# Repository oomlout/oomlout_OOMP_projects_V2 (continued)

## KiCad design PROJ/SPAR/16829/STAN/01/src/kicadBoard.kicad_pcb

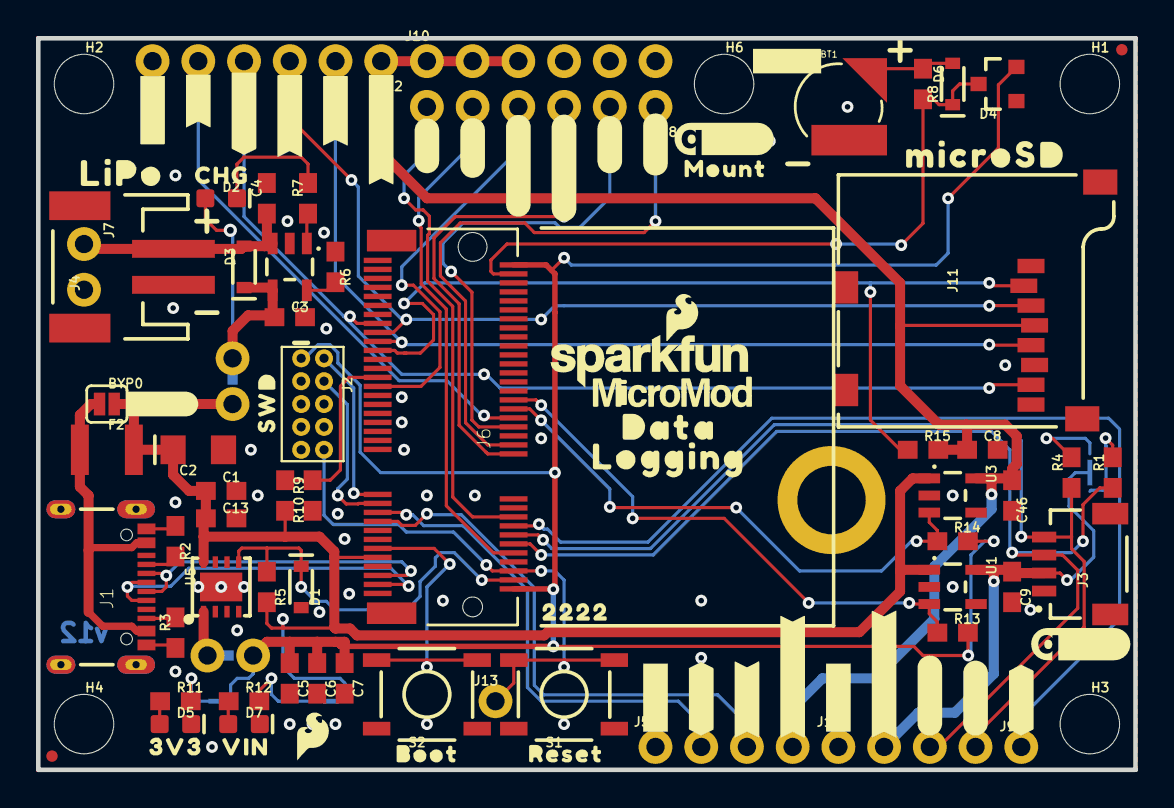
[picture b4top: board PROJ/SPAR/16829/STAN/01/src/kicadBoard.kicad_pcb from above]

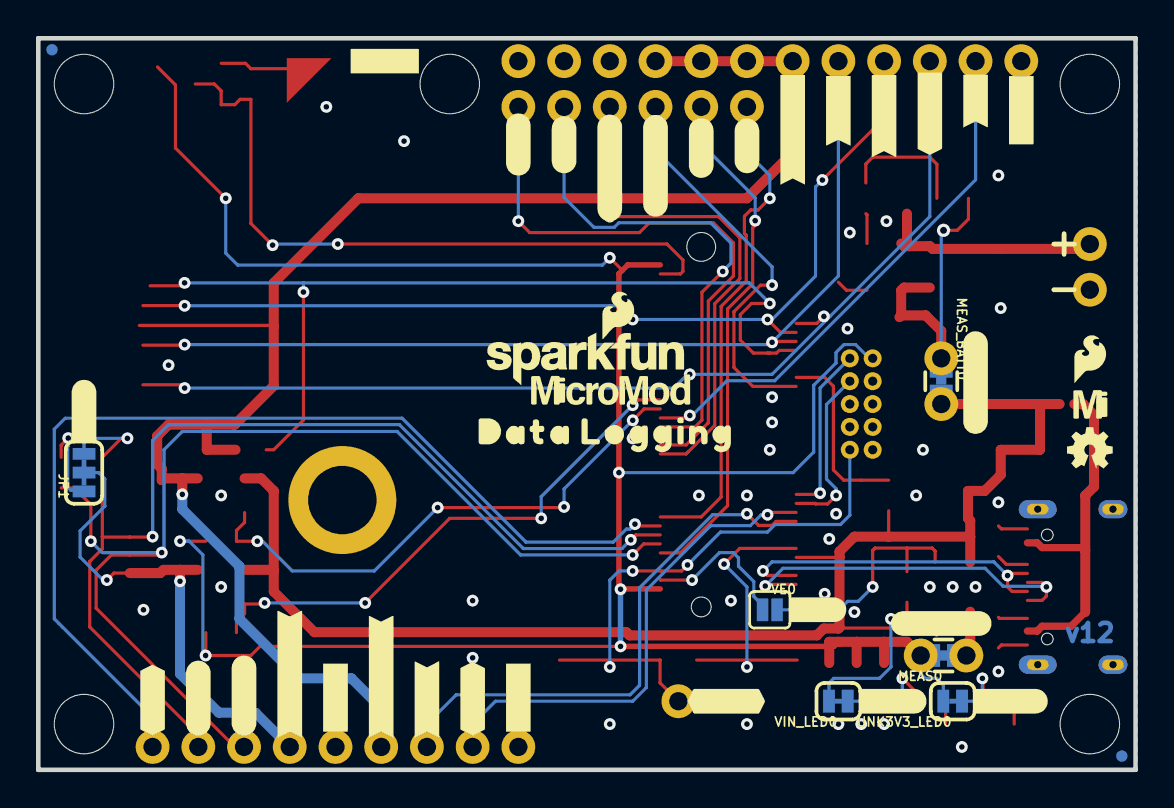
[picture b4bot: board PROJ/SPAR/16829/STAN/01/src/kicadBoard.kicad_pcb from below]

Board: 2 copper layers, 61.0 x 40.6 mm, 149 parts (44 on the bottom side), 49 nets.

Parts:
BT1: ML414H; ML414H_IV01E
BYP0: JUMPER-SMT_2_NO_SILK; SMT-JUMPER_2_NO_SILK
C1, C6, C46: 0.1uF; 0603
C2: 10uF; EIA3216
C3, C4: 4.7uF; 0603
C5, C8, C9: 1.0uF; 0603
C7, C13: 0.22uF; 0603
D1: 3.3V; SOD-323
D2, D7: Yellow; LED-0603
D3, D6: 3A/10V/280mV; SOD-323
D4: BAS70-05; SOT23-3
D5: RED; LED-0603
F2: 6V/2A; 1210
FD1, FD2, FD3, FD4: FIDUCIALUFIDUCIAL; FIDUCIAL-MICRO
FRAME1: FRAME-LEDGER; CREATIVE_COMMONS
H1, H2, H3, H4, H6: STAND-OFF
H5: STAND-OFF-REFLOW2.5MM_TALL; STAND-OFF-REFLOW-M2.5
J1: USB-C-16P-2LAYER-PADS
J2: JTAG; 2X5-PTH-1.27MM
J3: QWIIC_RIGHT_ANGLE; JST04_1MM_RA
J4: JST-2-SMD
J5: UART; 1X04_NO_SILK
J6: MICROMOD-2222-C; M.2-CONNECTOR-E
J7: 1X02_NO_SILK
J8: Dedicated; 1X06_NO_SILK
J9, J13: 1X01_NO_SILK
J10: 1X06_NO_SILK
J11: microSD; MICRO-SD-SOCKET
J12: SPI; 1X06_NO_SILK
J14: I2C; 1X04_NO_SILK
JP1: SMT-JUMPER_3_2-NC_TRACE_SILK
LOGO1, LOGO4: SFE_LOGO_NAME_FLAME.1_INCH; SFE_LOGO_NAME_FLAME_.1
LOGO2, LOGO5: QWIIC_LOGO_CONNECTOR; QWIIC_5.5MM
LOGO3: OSHW-LOGOMINI; OSHW-LOGO-MINI
MEAS0: COMBO-JUMPER_2_NC_TRACE
MEAS_BATT0: COMBO-JUMPER_2_NC_TRACE
R1, R4, R6: 2.2k; 0603
R2, R3: 5.1k; 0603
R5, R13, R14, R15: 100k; 0603
R7, R11: 1k; 0603
R8: 3.3k; 0603
R9: 10k; 0603
R10: 20k; 0603
R12: 4.7k; 0603
S1: Reset; TACTILE_SWITCH_SMD_5.2MM
S2: BOOT; TACTILE_SWITCH_SMD_5.2MM
U1, U3: 3.3V; SOT23-5
U2: MCP73831; SOT23-5
U5: AP7361C-33; UDFN-8
U$1, U$66: SFE_LOGO_FLAME_.1
U$2, U$76: #D1#0
U$3, U$77: #D0#0
U$4: #3V3#2
U$5: #BATT#0
U$6, U$18, U$24, U$27, U$32, U$34, U$36, U$42: #GND#0
U$7, U$8: #SCK#0
U$9, U$81: #PWM1#1
U$10, U$80: #PWM0#0
U$11: MICROSD0
U$12, U$79: #A1#2
U$13, U$78: #A0#3
U$14: MOUNT0
U$15: LIPO0
U$16, U$23: DATA0
U$17, U$86: #RX1#1
U$19, U$26: LOGGING1
U$20: 22220
U$21, U$89: #TX1#2
U$22: #I2C#0
U$25, U$90: #G1#3V3#0
U$28: #MEAS#3
U$29, U$83: #G2#3V3#3
U$30: #RST#0
U$31, U$88: #SDA#4
U$33: #VIN#1
U$35, U$87: #SCL#5
U$37, U$63: MICROMOD_LOGO_.35
U$38, U$82: ##INT##6
U$39, U$40: #CIPO#0
U$41: #VE#0
U$50, U$51: ##CS##0
U$62: MICROMOD_MI_LOGO_.35
U$64, U$65: #G1_3V3#0
U$72, U$73: #COPI#0
U$91: BOOT0
U$92: RESET1
U$93: 3V30
U$94: VIN1
U$95: #BYP#3
U$96: CHG1
U$97: SWD0
UNK3V3_LED0: SMT-JUMPER_2_NC_TRACE_SILK
VE0: SMT-JUMPER_2_NO_SILK
VIN_LED0: SMT-JUMPER_2_NC_TRACE_SILK

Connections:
3.3V: C5.1, C6.1, C7.1, D4.2, J2.1, J6.2, J6.74, MEAS0.2, MEAS0.4, R13.2, R14.2, UNK3V3_LED0.2
3.3V_EN: J6.4, VE0.1
3.3V_EN_VE: D1.C, R5.1, U5.5, VE0.2
3.3V_LP: C8.1, C46.1, J5.4, J10.1, J10.2, J10.3, J11.VCC, J12.1, R15.2, U3.5
5V: C3.1, D2.A, D3.C, MEAS_BATT0.1, MEAS_BATT0.3, U2.4
A0: J6.34, J8.1
A1: J6.38, J8.2
CHG_LED: R7.1, U2.1
D0: J6.10, J8.5
D1: J6.18, J8.6
GND: BT1.-, C1.2, C2.-, C3.2, C4.2, C5.2, C6.2, C7.2, C8.2, C9.2, C13.2, C46.2, D1.A, D5.C, D7.C, H5.1, J1.GND, J1.GND2, J2.3, J2.5, J2.9, J3.1, J4.1, J5.1, J6.1, J6.7, J6.33, J6.36, J6.39, J6.45, J6.75, J7.2, J10.4, J10.5, J10.6, J11.CD1, J11.GND, J11.GND1, J11.GND3, J12.6, J14.1, R2.1, R3.1, R6.1, R9.1, S1.1, S1.2, S2.1, S2.2, U1.2, U2.2, U3.2, U5.4, U5.EP
HEADER_~CS: J6.40, J12.5
I2C_SCL: J3.4, J6.14, J14.4, R4.1
I2C_SDA: J3.3, J6.12, J14.3, R1.1
I2C_~INT: J6.16, J9.1
unnamed: MEAS0.1, MEAS0.3, U5.1
unnamed: JP1.3, R4.2
unnamed: JP1.1, R1.2
unnamed: D2.C, R7.2
unnamed: D5.A, R11.1
unnamed: R11.2, UNK3V3_LED0.1
unnamed: R6.2, U2.5
unnamed: R12.2, VIN_LED0.1
unnamed: D7.A, R12.1
unnamed: J1.A5, R2.2
unnamed: J1.B5, R3.2
unnamed: BT1.+, D6.A, R8.1
PERIPHERAL_PWR_CTRL: J6.42, R14.1, U3.3
PWM0: J6.32, J8.3
PWM1: J6.47, J8.4
QWIIC_PWR: C9.1, J3.2, J14.2, JP1.2, U1.5
QWIIC_PWR_CTRL: J6.44, R13.1, U1.3
RTC_3V: D4.3, D6.C, J6.72, R8.2
RX1: J5.2, J6.19
SD_~CS: J6.55, J11.CS/DAT3, R15.1
SPI_CIPO: J6.61, J11.DO/DAT0, J12.4
SPI_COPI: J6.59, J11.DI/CMD, J12.3
SPI_SCK: J6.57, J11.SCLK, J12.2
SWDCK: J2.4, J6.21
SWDIO: J2.2, J6.23
TX1: J5.3, J6.17
USB_D+: J1.A6, J1.B6, J6.3
USB_D-: J1.A7, J1.B7, J6.5
VIN: BYP0.2, C1.1, C2.+, C13.1, F2.2, J6.9, MEAS_BATT0.2, MEAS_BATT0.4, R5.2, R10.2, U1.1, U3.1, U5.8, VIN_LED0.2
VIN/3: J6.49, R9.2, R10.1
V_BATT: C4.1, D3.A, J4.2, J7.1, U2.3
V_USB: BYP0.1, F2.1, J1.VBUS1, J1.VBUS2
~BOOT: J6.11, S2.3, S2.4
~RESET: J2.10, J6.6, J13.1, S1.3, S1.4

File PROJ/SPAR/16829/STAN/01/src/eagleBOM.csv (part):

"Part";"Value";"Device";"Package";"Description";"DESIGNER";"PROD_ID";"REV";"SF_ID";"VALUE";
"3V3_LED";"";"JUMPER-SMT_2_NC_TRACE_SILK";"SMT-JUMPER_2_NC_TRACE_SILK";"Normally closed trace jumper";"";"";"";"";"";
"BT1";"ML414H";"ML414H_IV01E_BATTERY";"ML414H_IV01E";"SEIKO ML414H-IV01E Reflowable Lithium Battery";"";"BATT-14267";"";"";"";
"BYP";"JUMPER-SMT_2_NO_SILK";"JUMPER-SMT_2_NO_SILK";"SMT-JUMPER_2_NO_SILK";"Normally open jumper";"";"";"";"";"";
"C1";"0.1uF";"0.1UF-0603-25V-(+80/-20%)";"0603";"0.1µF ceramic capacitors";"";"CAP-00810";"";"";"0.1uF";
"C2";"10uF";"10UF-POLAR-EIA3216-16V-10%(TANT)";"EIA3216";"10.0µF polarized capacitors";"";"CAP-00811";"";"";"10uF";
"C3";"4.7uF";"4.7UF-0603-35V-(20%)";"0603";"4.7µF ceramic capacitors";"";"CAP-14106";"";"";"4.7uF";
"C4";"4.7uF";"4.7UF-0603-6.3V-(10%)";"0603";"4.7µF ceramic capacitors";"";"CAP-08280";"";"";"4.7uF";
"C5";"1.0uF";"1.0UF-0603-16V-10%";"0603";"1µF ceramic capacitors";"";"CAP-00868";"";"";"1.0uF";
"C6";"0.1uF";"0.1UF-0603-25V-(+80/-20%)";"0603";"0.1µF ceramic capacitors";"";"CAP-00810";"";"";"0.1uF";
"C7";"0.22uF";"0.22UF-0603-25V-10%";"0603";"0.22µF ceramic capacitors";"";"CAP-07822";"";"";"0.22uF";
"C8";"1.0uF";"1.0UF-0603-16V-10%";"0603";"1µF ceramic capacitors";"";"CAP-00868";"";"";"1.0uF";
"C9";"1.0uF";"1.0UF-0603-16V-10%";"0603";"1µF ceramic capacitors";"";"CAP-00868";"";"";"1.0uF";
"C13";"0.22uF";"0.22UF-0603-25V-10%";"0603";"0.22µF ceramic capacitors";"";"CAP-07822";"";"";"0.22uF";
"C46";"0.1uF";"0.1UF-0603-25V-(+80/-20%)";"0603";"0.1µF ceramic capacitors";"";"CAP-00810";"";"";"0.1uF";
"D1";"3.3V";"DIODE-ZENER-MM3Z3V3T1G";"SOD-323";"Zener Diode";"";"DIO-11284";"";"";"3.3V";
"D2";"Yellow";"LED-YELLOW0603";"LED-0603";"Yellow SMD LED";"";"DIO-09003";"";"";"Yellow";
"D3";"3A/10V/280mV";"DIODE-SCHOTTKY-BAT60A";"SOD-323";"Schottky diode";"";"DIO-14072";"";"";"3A/10V/280mV";
"D4";"BAS70-05";"DIODE-SCHOTTKY-DUAL";"SOT23-3";"Diodes Incorporated - BAS70-05 Dual Schottky Diode";"";"DIO-14829";"";"";"BAS70-05";
"D5";"RED";"LED-RED0603";"LED-0603";"Red SMD LED";"";"DIO-00819";"";"";"RED";
"D6";"3A/10V/280mV";"DIODE-SCHOTTKY-BAT60A";"SOD-323";"Schottky diode";"";"DIO-14072";"";"";"3A/10V/280mV";
"D7";"Yellow";"LED-YELLOW0603";"LED-0603";"Yellow SMD LED";"";"DIO-09003";"";"";"Yellow";
"F2";"6V/2A";"PPTC_6V2A";"1210";"Resettable Fuse PPTC";"";"RES-14313";"";"";"6V/2A";
"FD1";"FIDUCIALUFIDUCIAL";"FIDUCIALUFIDUCIAL";"FIDUCIAL-MICRO";"Fiducial Alignment Points";"";"";"";"";"";
"FD2";"FIDUCIALUFIDUCIAL";"FIDUCIALUFIDUCIAL";"FIDUCIAL-MICRO";"Fiducial Alignment Points";"";"";"";"";"";
"FD3";"FIDUCIALUFIDUCIAL";"FIDUCIALUFIDUCIAL";"FIDUCIAL-MICRO";"Fiducial Alignment Points";"";"";"";"";"";
"FD4";"FIDUCIALUFIDUCIAL";"FIDUCIALUFIDUCIAL";"FIDUCIAL-MICRO";"Fiducial Alignment Points";"";"";"";"";"";
"FRAME1";"FRAME-LEDGER";"FRAME-LEDGER";"CREATIVE_COMMONS";"Schematic Frame - Ledger";"";"";"";"";"";
"H1";"STAND-OFF";"STAND-OFF";"STAND-OFF";"Stand Off";"";"";"";"";"";
"H2";"STAND-OFF";"STAND-OFF";"STAND-OFF";"Stand Off";"";"";"";"";"";
"H3";"STAND-OFF";"STAND-OFF";"STAND-OFF";"Stand Off";"";"";"";"";"";
"H4";"STAND-OFF";"STAND-OFF";"STAND-OFF";"Stand Off";"";"";"";"";"";
"H5";"STAND-OFF-REFLOW2.5MM_TALL";"STAND-OFF-REFLOW2.5MM_TALL";"STAND-OFF-REFLOW-M2.5";"Stand Off Reflow Compatible";"";"HW-14899";"";"";"";
"J1";"";"USB_C_2-LAYER_PADS";"USB-C-16P-2LAYER-PADS";"USB Type C 16Pin Connector";"";"CONN-14122";"";"";"";
"J2";"JTAG";"CORTEX_JTAG_DEBUG_MINIMUM_PTH";"2X5-PTH-1.27MM";"Cortex Debug Connector - 10 pin";"";"";"";"";"";
"J3";"QWIIC_RIGHT_ANGLE";"QWIIC_CONNECTORJS-1MM";"JST04_1MM_RA";"SparkFun I2C Standard Qwiic Connector";"";"CONN-13694";"";"";"QWIIC_RIGHT_ANGLE";
"J4";"";"JST_2MM_MALE";"JST-2-SMD";"JST 2MM MALE RA CONNECTOR";"";"CONN-11443";"";"PRT-08612";"";
"J5";"UART";"CONN_041X04_NO_SILK";"1X04_NO_SILK";"Multi connection point. Often used as Generic Header-pin footprint for 0.1 inch spaced/style header connections";"";"CONN-09696";"";"";"";
"J6";"MICROMOD-2222-C";"MICROMOD-2222-C";"M.2-CONNECTOR-E";"MicroMod Connector";"";"CONN-14877";"";"";"";
"J7";"";"CONN_021X02_NO_SILK";"1X02_NO_SILK";"Multi connection point. Often used as Generic Header-pin footprint for 0.1 inch spaced/style header connections";"";"";"";"";"";
"J8";"Dedicated";"CONN_06NO_SILK_NO_POP";"1X06_NO_SILK";"Multi connection point. Often used as Generic Header-pin footprint for 0.1 inch spaced/style header connections";"";"";"";"";"";
"J9";"";"CONN_01PTH_NO_SILK_YES_STOP";"1X01_NO_SILK";"Single connection point. Often used as Generic Header-pin footprint for 0.1 inch spaced/style header connections";"";"";"";"";"";
"J10";"";"CONN_06NO_SILK_NO_POP";"1X06_NO_SILK";"Multi connection point. Often used as Generic Header-pin footprint for 0.1 inch spaced/style header connections";"";"";"";"";"";
"J11";"microSD";"MICRO-SD-SDIOPUSH-PUSH";"MICRO-SD-SOCKET";"microSD Socket for Transflash";"";"CONN-07820";"";"";"";
"J12";"SPI";"CONN_06NO_SILK_NO_POP";"1X06_NO_SILK";"Multi connection point. Often used as Generic Header-pin footprint for 0.1 inch spaced/style header connections";"";"";"";"";"";
"J13";"";"CONN_01PTH_NO_SILK_YES_STOP";"1X01_NO_SILK";"Single connection point. Often used as Generic Header-pin footprint for 0.1 inch spaced/style header connections";"";"";"";"";"";
"J14";"I2C";"I2C_STANDARD_NO_SILK";"1X04_NO_SILK";"SparkFun I2C Standard Pinout Header";"";"";"";"";"";
"JP1";"";"JUMPER-SMT_3_2-NC_TRACE_SILK";"SMT-JUMPER_3_2-NC_TRACE_SILK";"Normally closed trace jumper (2 of 2 connections)";"";"";"";"";"";
"LOGO1";"SFE_LOGO_NAME_FLAME.1_INCH";"SFE_LOGO_NAME_FLAME.1_INCH";"SFE_LOGO_NAME_FLAME_.1";"SparkFun Font Logo w/ Flame";"";"";"";"";"";
"LOGO2";"QWIIC_LOGO_CONNECTOR";"QWIIC_LOGO_CONNECTOR";"QWIIC_5.5MM";"Qwiic Logos for placement on schematic and PCB. The 5.5mm silk logo is best for placing next to Qwiic connector.";"";"";"";"";"";
"LOGO3";"OSHW-LOGOMINI";"OSHW-LOGOMINI";"OSHW-LOGO-MINI";"Open-Source Hardware (OSHW) Logo";"";"";"";"";"";
"MEAS";"";"JUMPER-COMBO_2_NC_TRACE";"COMBO-JUMPER_2_NC_TRACE";"";"";"";"";"";"";
"MEAS_BATT";"";"JUMPER-COMBO_2_NC_TRACE";"COMBO-JUMPER_2_NC_TRACE";"";"";"";"";"";"";
"R1";"2.2k";"2.2KOHM-0603-1/10W-1%";"0603";"2.2kΩ resistor";"";"RES-08272";"";"";"2.2k";
"R2";"5.1k";"5.1KOHM5.1KOHM-0603-1/10W-1%";"0603";"";"";"RES-12083";"";"";"5.1k";
"R3";"5.1k";"5.1KOHM5.1KOHM-0603-1/10W-1%";"0603";"";"";"RES-12083";"";"";"5.1k";
"R4";"2.2k";"2.2KOHM-0603-1/10W-1%";"0603";"2.2kΩ resistor";"";"RES-08272";"";"";"2.2k";
"R5";"100k";"100KOHM-0603-1/10W-1%";"0603";"100kΩ resistor";"";"RES-07828";"";"";"100k";
"R6";"2.2k";"2.2KOHM-0603-1/10W-1%";"0603";"2.2kΩ resistor";"";"RES-08272";"";"";"2.2k";
"R7";"1k";"1KOHM-0603-1/10W-1%";"0603";"1kΩ resistor";"";"RES-07856";"";"";"1k";
"R8";"3.3k";"3.3KOHM-0603-1/10W-1%";"0603";"3.3kΩ resistor";"";"RES-07851";"";"";"3.3k";
"R9";"10k";"10KOHM-0603-1/10W-1%";"0603";"10kΩ resistor";"";"RES-00824";"";"";"10k";
"R10";"20k";"20KOHM-0603-1/10W-1%";"0603";"20kΩ resistor";"";"RES-09383";"";"";"20k";
"R11";"1k";"1KOHM-0603-1/10W-1%";"0603";"1kΩ resistor";"";"RES-07856";"";"";"1k";
"R12";"4.7k";"4.7KOHM-0603-1/10W-1%";"0603";"4.7kΩ resistor";"";"RES-07857";"";"";"4.7k";
"R13";"100k";"100KOHM-0603-1/10W-1%";"0603";"100kΩ resistor";"";"RES-07828";"";"";"100k";
"R14";"100k";"100KOHM-0603-1/10W-1%";"0603";"100kΩ resistor";"";"RES-07828";"";"";"100k";
"R15";"100k";"100KOHM-0603-1/10W-1%";"0603";"100kΩ resistor";"";"RES-07828";"";"";"100k";
"S1";"Reset";"MOMENTARY-SWITCH-SPST-SMD-5.2-TALL-REDUNDANT";"TACTILE_SWITCH_SMD_5.2MM";"Momentary Switch (Pushbutton) - SPST";"";"SWCH-14139";"";"";"";
"S2";"BOOT";"MOMENTARY-SWITCH-SPST-SMD-5.2-TALL-REDUNDANT";"TACTILE_SWITCH_SMD_5.2MM";"Momentary Switch (Pushbutton) - SPST";"";"SWCH-14139";"";"";"";
"U1";"3.3V";"V_REG_AP2112K-3.3V";"SOT23-5";"AP2112 - 600mA CMOS LDO Regulator w/ Enable";"";"VREG-12457";"";"";"3.3V";
"U2";"MCP73831";"MCP73831";"SOT23-5";"MCP73831T Li-Ion, Li-Pol Controller";"";"IC-09995";"";"";"";
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
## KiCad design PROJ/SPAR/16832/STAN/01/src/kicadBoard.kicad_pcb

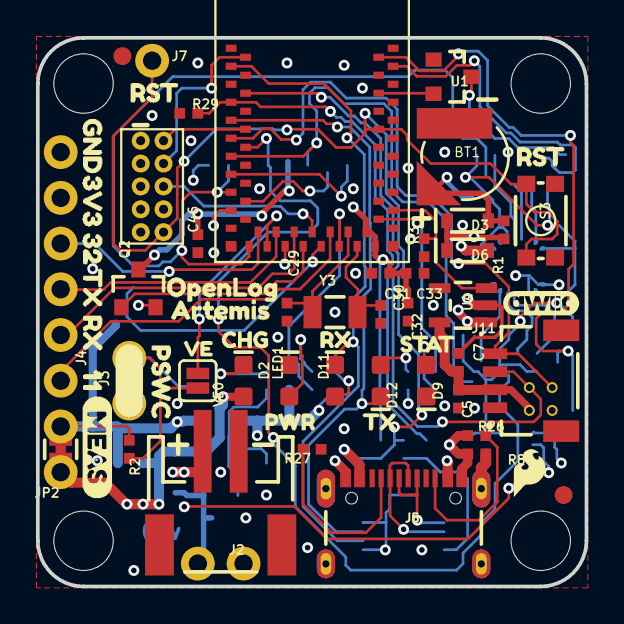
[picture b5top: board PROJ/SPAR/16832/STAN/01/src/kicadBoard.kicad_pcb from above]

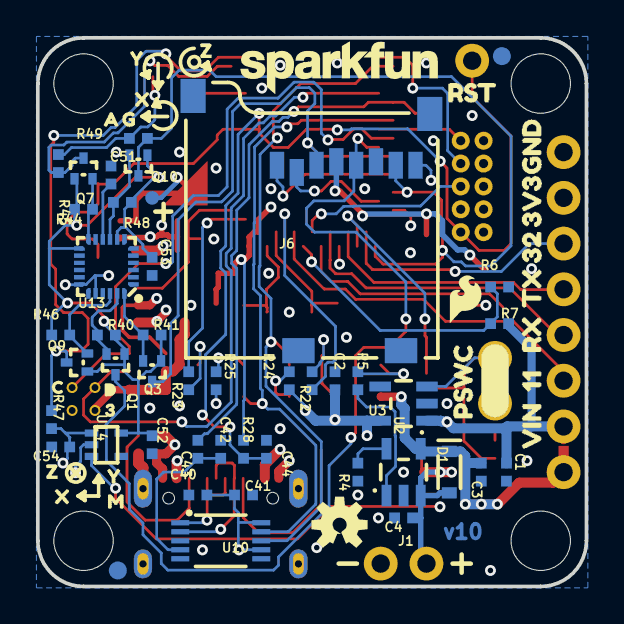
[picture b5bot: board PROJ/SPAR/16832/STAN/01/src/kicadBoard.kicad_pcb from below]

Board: 4 copper layers, 30.5 x 30.5 mm, 140 parts (74 on the bottom side), 61 nets.

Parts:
BT1: ML414H; ML414H_IV01E
C1, C33, C53, C54: 1.0uF; 0402-TIGHT
C2, C7: 2.2uF; 0402-TIGHT
C3, C4: 4.7uF; 0402-TIGHT
C5, C31, C41, C42, C43, C46, C51, C52: 0.1uF; 0402-TIGHT
C29, C30: 15pF; 0402-TIGHT
C32: 10uF; 0402-TIGHT
C40: 10nF; 0402-TIGHT
C44: 1.0nF; 0402-TIGHT
D1, D3: 3A/10V/280mV; SOD-323
D2, D11: Yellow; LED-0603
D6: 1A/23V/620mV; SOD-323
D9: BLUE; LED-0603
D12: GREEN; LED-0603
FD1, FD2, FD3, FD4: FIDUCIAL1X2; FIDUCIAL-1X2
FRAME1: FRAME-LEDGER; CREATIVE_COMMONS
GND0: TEST-POINTTP_15TH_THRU; TP_15TH
H1, H2, H3, H4: STAND-OFF
J1, J3: 1X02_NO_SILK
J2: JST-2-SMD
J4: 1X06_NO_SILK
J5: USB-C-16P_4LAYER-PADS
J6: MICRO-SD; MICRO-SD-SOCKET
J7: 1X01_NO_SILK
J11: QWIIC_RIGHT_ANGLE; JST04_1MM_RA
J14: CORTEX_JTAG; 2X5-PTH-1.27MM
JP2: MEAS; COMBO-JUMPER_2_NC_TRACE
LED1: RED; LED-0603
LOGO1: SFE_LOGO_NAME.1_INCH; SFE_LOGO_NAME_.1
LOGO2: OSHW-LOGOS; OSHW-LOGO-S
LOGO3: SPECIAL_INSTRUCTIONS-ORDERING; ORDERING_INSTRUCTIONS
LOGO4, LOGO5: SFE_LOGO_FLAME.1_INCH; SFE_LOGO_FLAME_.1
Q1, Q3, Q7, Q9, Q10: 20V/0.2A/8MHz/1.2Ω/1Vth; SOT-416FL
Q2: 20V/4.2A/52mΩ/1.4W; SOT23-3
QWIIC_3.3V0: TEST-POINTTP_15TH_THRU; TP_15TH
R1, R4, R40, R41, R44, R45, R46, R47, R48: 2.2k; 0402-TIGHT
R2: 330K; 0402-TIGHT
R3: 220k; 0402-TIGHT
R5, R22, R23, R24, R25: 1k; 0402-TIGHT
R6: 1M; 0402-TIGHT
R7: 2M; 0402-TIGHT
R8: 0; 0402-TIGHT
R26, R27: 5.1k; 0402-TIGHT
R28: 100k; 0402-TIGHT
R29: 220KOHM-0402T-1/16W-1%; 0402-TIGHT
R49: DNP; 0402-TIGHT
S3: RESET; TACTILE_SWITCH_SMD_4.6X2.8MM
SCL0: TEST-POINTTP_15TH_THRU; TP_15TH
SDA0: TEST-POINTTP_15TH_THRU; TP_15TH
TP1: TEST-POINT3; PAD.03X.03
U1: 3.0V Supervisor; SOT23-3
U2: MCP73831; SOT23-5
U3, U4: 3.3V; SOT23-5
U8: ARTEMIS_MODULE; ARTEMIS_FP
U10: CH340E; MSOP10
U13: 9DoF IMU; QFN24-3X3-ICM-20948
U14: 1.8V/100mA; SC70
U$1: QWIIC#LOGO#JPG
U$2: CHG2
U$3: PWR0
U$4: RX4
U$5: STAT5
U$6: VE0
U$7: TX3
U$8, U$12: RST0
U$9: ARTEMIS13
U$10, U$11: PSWC0
U$13: C0
U$14: D0
U$15: 30
U$27: MEAS3
U$28: OPENLOG12
U$32: RST9
U$33: VIN8
U$34, U$35: 3V34
U$36, U$37: 113
U$38, U$39: 322
U$40, U$41: GND5
U$42, U$54: RX1
U$43, U$49: X0
U$44, U$50: Y1
U$45, U$51: Z2
U$46: G5
U$47: A4
U$48: M3
U$55, U$56: TX0
VE0: SMT-JUMPER_2_NO_SILK
Y3: 32.768kHz; CRYSTAL-SMD-3.2X1.5MM

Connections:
3.3V: C2.1, C40.1, C41.1, C54.1, D6.A, J4.5, J14.1, Q2.2, R24.2, R25.2, R45.2, R47.2, R49.2, U1.3, U3.5, U10.7, U10.10, U14.1
5V: C3.1, D1.C, D2.A, J5.VBUS1, J5.VBUS2, JP2.1, JP2.3, U2.4
ARTEMIS_BOOT: C43.2, R29.2, U8.BOOT
ARTEMIS_RX0: D11.C, U8.RXI-0, U10.8
ARTEMIS_SWDCK: J14.4, U8.SWDCK
ARTEMIS_SWDIO: J14.2, U8.SWDIO
ARTEMIS_TX0: D12.C, U8.TXO-0, U10.9
ARTEMIS_~AD11: J4.1, U8.~AD11
ARTEMIS_~AD12/TX1: J4.3, U8.~AD12
ARTEMIS_~AD13/RX1: J4.2, U8.~AD13
ARTEMIS_~AD32: J4.4, U8.~AD32
ARTEMIS_~RESET: C42.2, C44.1, J7.1, J14.10, R28.1, S3.3, S3.4, U8.~RST
ARTEMIS_~RTS: C42.1, C43.1, U10.4
CC3: J5.B5, R26.2
CC4: J5.A5, R27.2
CHG_LED: R5.1, U2.1
D+2: J5.A6, J5.B6, U10.1
D-2: J5.A7, J5.B7, U10.2
DAT1: J6.DAT1, U8.~D26
DAT2: J6.DAT2, U8.~D4
GND: BT1.-, C1.2, C2.2, C3.2, C4.2, C5.2, C7.2, C29.1, C30.1, C31.1, C32.2, C33.2, C40.2, C41.2, C44.2, C46.2, C51.2, C52.2, C53.2, C54.2, D9.C, GND0.P$1, J1.2, J2.1, J3.2, J4.6, J5.GND, J5.GND2, J6.CD1, J6.GND, J6.GND1, J6.GND3, J11.1, J14.3, J14.5, J14.9, LED1.C, R3.1, R4.1, R6.1, R8.1, R26.1, R27.1, R29.1, S3.1, S3.2, U1.1, U2.2, U3.2, U4.2, U8.GND@1, U8.GND@22, U8.GND@38, U8.GND@39, U8.GND@47, U8.GND@59, U10.3, U13.18, U13.20, U14.2
ICM-20948-LV_#_1.8V: C52.1, C53.1, Q1.1, Q3.1, Q7.1, Q9.1, Q10.1, R40.2, R41.2, R44.2, R46.2, R48.2, U13.8, U13.13, U14.5
ICM-20948-LV_INT: Q7.2, R44.1, U13.12
ICM-20948-LV_SCK: Q1.2, R40.1, U13.23
ICM-20948-LV_SDI: Q3.2, R41.1, U13.24
ICM-20948-LV_SDO: Q10.2, R48.1, U13.9
ICM-20948-LV_~CS: Q9.2, R46.1, U13.22
ICM_INT: Q7.3, R45.1, U8.~D37
ICM_PWR: U8.~D27, U14.3
ICM_~CS: Q9.3, R47.1, U8.~D44
MICROSD_PWR: Q2.1, U8.D15
MICROSD_~CS: J6.CS/DAT3, U8.~D23
unnamed: J5.SHLD1, J5.SHLD2, J5.SHLD3, J5.SHLD4, R8.2
unnamed: R4.2, U2.5
unnamed: D2.C, R5.2
unnamed: C29.2, U8.XO, Y3.P$2
unnamed: C30.2, U8.XI, Y3.P$1
unnamed: LED1.A, R22.1
unnamed: D9.A, R23.1
unnamed: D12.A, R25.1
unnamed: D11.A, R24.1
unnamed: C51.1, U13.10
PWR_LED: R22.2, U8.~AD29
QWIIC_3.3V: C5.1, C7.1, J11.2, QWIIC_3.3V0.P$1, U4.5
QWIIC_PWR: R3.2, U4.3, U8.~D18
RTC_BAT+: BT1.+, D3.A, R1.1, TP1.P$1
SCK: J6.SCLK, Q1.3, U8.~D5
SCL: J11.4, SCL0.P$1, U8.D8
SDA: J11.3, SDA0.P$1, U8.D9
SDI: J6.DO/DAT0, Q10.3, R49.1, U8.~D6, U8.~D22
SDO: J6.DI/CMD, Q3.3, U8.D7
SD_PWR: C46.1, J6.VCC, Q2.3
STATLED: R23.2, U8.~D19
SWO: J14.6, U8.~AD33/SWO
VCC_1: C31.2, C32.1, C33.1, D3.C, D6.C, R1.2, R28.2, U8.VDD@36, U8.VDD@37
VIN: C1.1, JP2.2, JP2.4, R2.2, R7.2, U3.1, U4.1
VIN/3: R6.2, R7.1, U8.AD34
VREG_EN: J3.1, R2.1, U3.3, VE0.2
VREG_EN1: U8.~D25, VE0.1
V_BATT: C4.1, D1.A, J1.1, J2.2, U2.3
~POWER_LOSS: U1.2, U8.D3

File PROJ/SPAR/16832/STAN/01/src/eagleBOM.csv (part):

"Part";"Value";"Device";"Package";"Description";"DESIGNER";"PROD_ID";"REV";"SF_ID";"VALUE";
"BT1";"ML414H";"ML414H_IV01E_BATTERY";"ML414H_IV01E";"SEIKO ML414H-IV01E Reflowable Lithium Battery";"";"BATT-14267";"";"";"";
"C1";"1.0uF";"1.0UF-0402T-16V-10%";"0402-TIGHT";"1µF ceramic capacitors";"";"CAP-12417";"";"";"1.0uF";
"C2";"2.2uF";"2.2UF-0402_TIGHT-10V-10%-X5R";"0402-TIGHT";"2.2µF ceramic capacitors";"";"CAP-14232";"";"";"2.2uF";
"C3";"4.7uF";"4.7UF-0402_TIGHT-6.3V-20%-X5R";"0402-TIGHT";"4.7µF ceramic capacitors";"";"CAP-14240";"";"";"4.7uF";
"C4";"4.7uF";"4.7UF-0402_TIGHT-6.3V-20%-X5R";"0402-TIGHT";"4.7µF ceramic capacitors";"";"CAP-14240";"";"";"4.7uF";
"C5";"0.1uF";"0.1UF-0402T-6.3V-10%-X7R";"0402-TIGHT";"0.1µF ceramic capacitors";"";"CAP-14993";"";"";"0.1uF";
"C7";"2.2uF";"2.2UF-0402_TIGHT-10V-10%-X5R";"0402-TIGHT";"2.2µF ceramic capacitors";"";"CAP-14232";"";"";"2.2uF";
"C29";"15pF";"15PF-0402T-50V-5%";"0402-TIGHT";"15pF ceramic capacitors";"";"CAP-13063";"";"";"15pF";
"C30";"15pF";"15PF-0402T-50V-5%";"0402-TIGHT";"15pF ceramic capacitors";"";"CAP-13063";"";"";"15pF";
"C31";"0.1uF";"0.1UF-0402T-16V-10%";"0402-TIGHT";"0.1µF ceramic capacitors";"";"CAP-12416";"";"";"0.1uF";
"C32";"10uF";"10UF-0402T-6.3V-20%";"0402-TIGHT";"10.0µF ceramic capacitors";"";"CAP-14848";"";"";"10uF";
"C33";"1.0uF";"1.0UF-0402T-16V-10%";"0402-TIGHT";"1µF ceramic capacitors";"";"CAP-12417";"";"";"1.0uF";
"C40";"10nF";"10NF-0402T-25V-10%";"0402-TIGHT";"0.01uF/10nF/10,000pF ceramic capacitors";"";"CAP-14847";"";"";"10nF";
"C41";"0.1uF";"0.1UF-0402T-16V-10%";"0402-TIGHT";"0.1µF ceramic capacitors";"";"CAP-12416";"";"";"0.1uF";
"C42";"0.1uF";"0.1UF-0402T-16V-10%";"0402-TIGHT";"0.1µF ceramic capacitors";"";"CAP-12416";"";"";"0.1uF";
"C43";"0.1uF";"0.1UF-0402T-16V-10%";"0402-TIGHT";"0.1µF ceramic capacitors";"";"CAP-12416";"";"";"0.1uF";
"C44";"1.0nF";"1.0NF/1000PF-0402_TIGHT-50V-10%";"0402-TIGHT";"1nF/1,000pF ceramic capacitors";"";"CAP-14280";"";"";"1.0nF";
"C46";"0.1uF";"0.1UF-0402T-16V-10%";"0402-TIGHT";"0.1µF ceramic capacitors";"";"CAP-12416";"";"";"0.1uF";
"C51";"0.1uF";"0.1UF-0402T-16V-10%";"0402-TIGHT";"0.1µF ceramic capacitors";"";"CAP-12416";"";"";"0.1uF";
"C52";"0.1uF";"0.1UF-0402T-16V-10%";"0402-TIGHT";"0.1µF ceramic capacitors";"";"CAP-12416";"";"";"0.1uF";
"C53";"1.0uF";"1.0UF-0402T-16V-10%";"0402-TIGHT";"1µF ceramic capacitors";"";"CAP-12417";"";"";"1.0uF";
"C54";"1.0uF";"1.0UF-0402T-16V-10%";"0402-TIGHT";"1µF ceramic capacitors";"";"CAP-12417";"";"";"1.0uF";
"D1";"3A/10V/280mV";"DIODE-SCHOTTKY-BAT60A";"SOD-323";"Schottky diode";"";"DIO-14072";"";"";"3A/10V/280mV";
"D2";"Yellow";"LED-YELLOW0603";"LED-0603";"Yellow SMD LED";"";"DIO-09003";"";"";"Yellow";
"D3";"3A/10V/280mV";"DIODE-SCHOTTKY-BAT60A";"SOD-323";"Schottky diode";"";"DIO-14072";"";"";"3A/10V/280mV";
"D6";"1A/23V/620mV";"DIODE-SCHOTTKY-BAT20J";"SOD-323";"Schottky diode";"";"DIO-11623";"";"";"1A/23V/620mV";
"D9";"BLUE";"LED-BLUE0603";"LED-0603";"Blue SMD LED";"";"DIO-08575";"";"";"BLUE";
"D11";"Yellow";"LED-YELLOW0603";"LED-0603";"Yellow SMD LED";"";"DIO-09003";"";"";"Yellow";
"D12";"GREEN";"LED-GREEN0603";"LED-0603";"Green SMD LED";"";"DIO-00821";"";"";"GREEN";
"FD1";"FIDUCIAL1X2";"FIDUCIAL1X2";"FIDUCIAL-1X2";"Fiducial Alignment Points";"";"";"";"";"";
"FD2";"FIDUCIAL1X2";"FIDUCIAL1X2";"FIDUCIAL-1X2";"Fiducial Alignment Points";"";"";"";"";"";
"FD3";"FIDUCIAL1X2";"FIDUCIAL1X2";"FIDUCIAL-1X2";"Fiducial Alignment Points";"";"";"";"";"";
"FD4";"FIDUCIAL1X2";"FIDUCIAL1X2";"FIDUCIAL-1X2";"Fiducial Alignment Points";"";"";"";"";"";
"FRAME1";"FRAME-LEDGER";"FRAME-LEDGER";"CREATIVE_COMMONS";"Schematic Frame - Ledger";"";"";"";"";"";
"GND";"TEST-POINTTP_15TH_THRU";"TEST-POINTTP_15TH_THRU";"TP_15TH";"SparkFun Test Points";"";"";"";"";"";
"H1";"STAND-OFF";"STAND-OFF";"STAND-OFF";"Stand Off";"";"";"";"";"";
"H2";"STAND-OFF";"STAND-OFF";"STAND-OFF";"Stand Off";"";"";"";"";"";
"H3";"STAND-OFF";"STAND-OFF";"STAND-OFF";"Stand Off";"";"";"";"";"";
"H4";"STAND-OFF";"STAND-OFF";"STAND-OFF";"Stand Off";"";"";"";"";"";
"J1";"";"CONN_021X02_NO_SILK";"1X02_NO_SILK";"Multi connection point. Often used as Generic Header-pin footprint for 0.1 inch spaced/style header connections";"";"";"";"";"";
"J2";"";"JST_2MM_MALE";"JST-2-SMD";"JST 2MM MALE RA CONNECTOR";"";"CONN-11443";"";"PRT-08612";"";
"J3";"";"CONN_021X02_NO_SILK";"1X02_NO_SILK";"Multi connection point. Often used as Generic Header-pin footprint for 0.1 inch spaced/style header connections";"";"";"";"";"";
"J4";"";"CONN_06NO_SILK_NO_POP";"1X06_NO_SILK";"Multi connection point. Often used as Generic Header-pin footprint for 0.1 inch spaced/style header connections";"";"";"";"";"";
"J5";"";"USB_C_4-LAYER_PADS";"USB-C-16P_4LAYER-PADS";"USB Type C 16Pin Connector";"";"CONN-14122";"";"";"";
"J6";"MICRO-SD";"MICRO-SD-SDIOPUSH-PUSH";"MICRO-SD-SOCKET";"microSD Socket for Transflash";"";"CONN-07820";"";"";"";
"J7";"";"CONN_01PTH_NO_SILK_YES_STOP";"1X01_NO_SILK";"Single connection point. Often used as Generic Header-pin footprint for 0.1 inch spaced/style header connections";"";"";"";"";"";
"J11";"";"QWIIC_CONNECTORJS-1MM";"JST04_1MM_RA";"SparkFun I2C Standard Qwiic Connector";"";"CONN-13694";"";"";"QWIIC_RIGHT_ANGLE";
"J14";"CORTEX_JTAG";"CORTEX_JTAG_DEBUG_MINIMUM_PTH";"2X5-PTH-1.27MM";"Cortex Debug Connector - 10 pin";"";"";"";"";"";
"JP2";"MEAS";"JUMPER-COMBO_2_NC_TRACE";"COMBO-JUMPER_2_NC_TRACE";"";"";"";"";"";"";
"LED1";"RED";"LED-RED0603";"LED-0603";"Red SMD LED";"";"DIO-00819";"";"";"RED";
"LOGO1";"SFE_LOGO_NAME.1_INCH";"SFE_LOGO_NAME.1_INCH";"SFE_LOGO_NAME_.1";"SparkFun Font Logo";"";"";"";"";"";
"LOGO2";"OSHW-LOGOS";"OSHW-LOGOS";"OSHW-LOGO-S";"Open-Source Hardware (OSHW) Logo";"";"";"";"";"";
"LOGO3";"SPECIAL_INSTRUCTIONS-ORDERING";"SPECIAL_INSTRUCTIONS-ORDERING";"ORDERING_INSTRUCTIONS";"Special Ordering/Production Instructions Alert";"";"";"";"";"";
"LOGO4";"SFE_LOGO_FLAME.1_INCH";"SFE_LOGO_FLAME.1_INCH";"SFE_LOGO_FLAME_.1";"SparkFun Flame Logo";"";"";"";"";"";
"LOGO5";"SFE_LOGO_FLAME.1_INCH";"SFE_LOGO_FLAME.1_INCH";"SFE_LOGO_FLAME_.1";"SparkFun Flame Logo";"";"";"";"";"";
"Q1";"20V/0.2A/8MHz/1.2Ω/1Vth";"MOSFET-NCH-RE1C00UNTL";"SOT-416FL";"N-channel MOSFETs";"";"TRANS-14399";"";"";"20V/0.2A/8MHz/1.2Ω/1Vth";
"Q2";"20V/4.2A/52mΩ/1.4W";"MOSFET_PCH-DMG2305UX-7";"SOT23-3";"P-channel MOSFETs";"";"TRAN-14388";"";"";"20V/4.2A/52mΩ/1.4W";
"Q3";"20V/0.2A/8MHz/1.2Ω/1Vth";"MOSFET-NCH-RE1C00UNTL";"SOT-416FL";"N-channel MOSFETs";"";"TRANS-14399";"";"";"20V/0.2A/8MHz/1.2Ω/1Vth";
"Q7";"20V/0.2A/8MHz/1.2Ω/1Vth";"MOSFET-NCH-RE1C00UNTL";"SOT-416FL";"N-channel MOSFETs";"";"TRANS-14399";"";"";"20V/0.2A/8MHz/1.2Ω/1Vth";
"Q9";"20V/0.2A/8MHz/1.2Ω/1Vth";"MOSFET-NCH-RE1C00UNTL";"SOT-416FL";"N-channel MOSFETs";"";"TRANS-14399";"";"";"20V/0.2A/8MHz/1.2Ω/1Vth";
"Q10";"20V/0.2A/8MHz/1.2Ω/1Vth";"MOSFET-NCH-RE1C00UNTL";"SOT-416FL";"N-channel MOSFETs";"";"TRANS-14399";"";"";"20V/0.2A/8MHz/1.2Ω/1Vth";
"QWIIC_3.3V";"TEST-POINTTP_15TH_THRU";"TEST-POINTTP_15TH_THRU";"TP_15TH";"SparkFun Test Points";"";"";"";"";"";
"R1";"2.2k";"2.2KOHM-0402T-1/16W-1%";"0402-TIGHT";"2.2kΩ resistor";"";"RES-14341";"";"";"2.2k";
"R2";"330K";"330KOHM-0402T-1/16W-1%";"0402-TIGHT";"330kΩ resistor";"";"RES-15187";"";"";"330K";
"R3";"220k";"220KOHM-0402T-1/16W-1%";"0402-TIGHT";"220kΩ resistor";"";"RES-15094";"";"";"";
"R4";"2.2k";"2.2KOHM-0402T-1/16W-1%";"0402-TIGHT";"2.2kΩ resistor";"";"RES-14341";"";"";"2.2k";
"R5";"1k";"1KOHM-0402T-1/16W-1%";"0402-TIGHT";"1kΩ resistor";"";"RES-14342";"";"";"1k";
"R6";"1M";"1MOHM-0402T-1/16W-1%";"0402-TIGHT";"1MΩ resistor";"";"RES-15185";"";"";"1M";
"R7";"2M";"2MOHM-0402T-1/16W-1%";"0402-TIGHT";"2MΩ resistor";"";"RES-15186";"";"";"2M";
"R8";"0";"0OHM-0402T-1/10W";"0402-TIGHT";"0Ω resistor";"";"RES-14244";"";"";"0";
"R22";"1k";"1KOHM-0402T-1/16W-1%";"0402-TIGHT";"1kΩ resistor";"";"RES-14342";"";"";"1k";
"R23";"1k";"1KOHM-0402T-1/16W-1%";"0402-TIGHT";"1kΩ resistor";"";"RES-14342";"";"";"1k";
"R24";"1k";"1KOHM-0402T-1/16W-1%";"0402-TIGHT";"1kΩ resistor";"";"RES-14342";"";"";"1k";
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
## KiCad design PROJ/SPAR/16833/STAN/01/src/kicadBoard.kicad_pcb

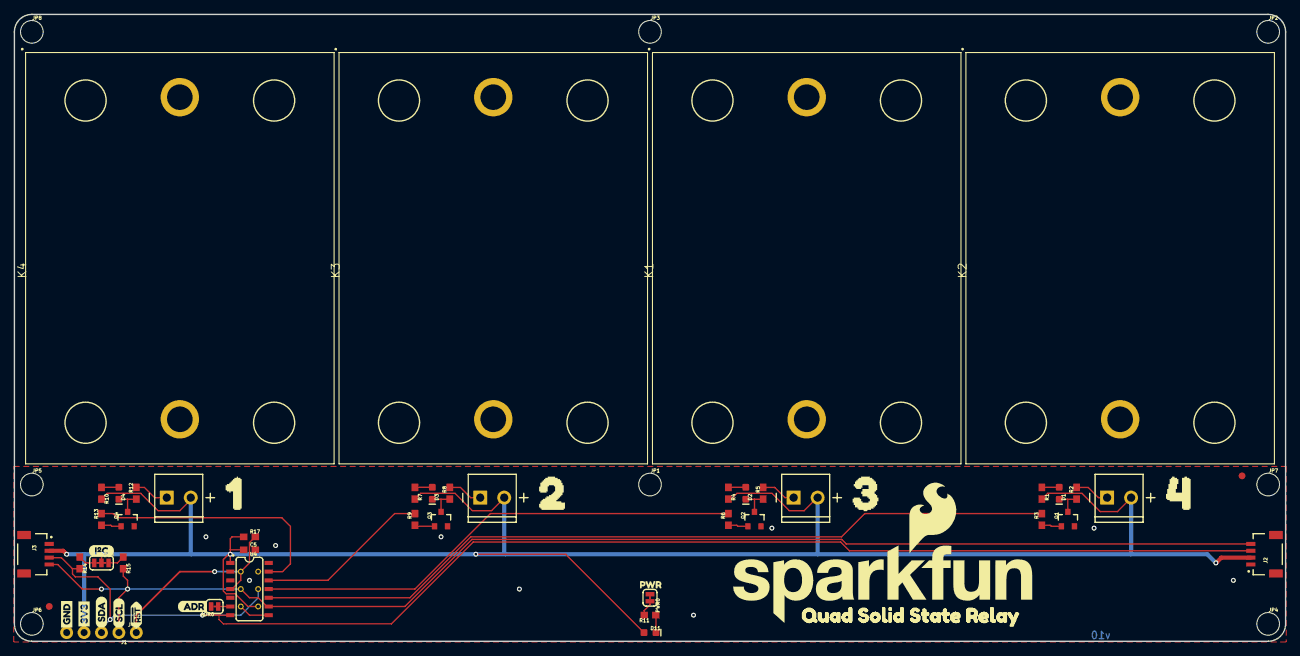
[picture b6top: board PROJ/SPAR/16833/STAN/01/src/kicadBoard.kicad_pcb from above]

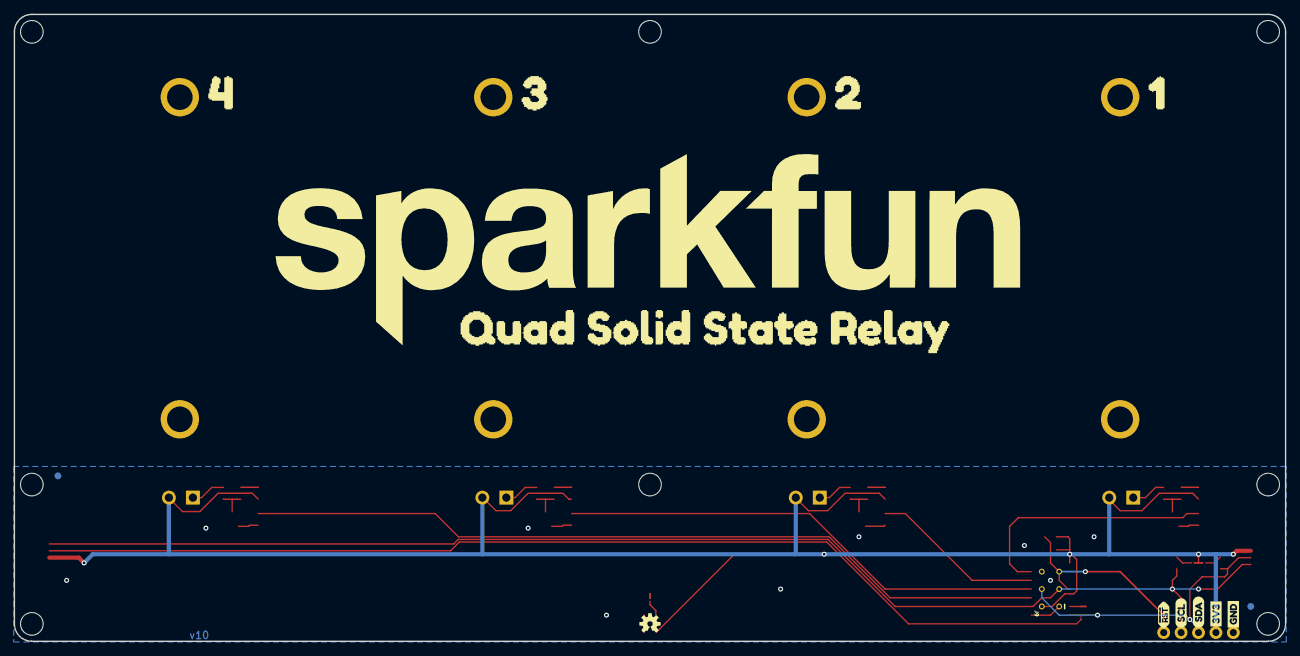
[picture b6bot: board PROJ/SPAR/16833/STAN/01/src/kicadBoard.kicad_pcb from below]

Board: 2 copper layers, 185.4 x 91.4 mm, 79 parts (15 on the bottom side), 31 nets.

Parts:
ADR0: JUMPER-SMT_2_NC_TRACE_SILK; SMT-JUMPER_2_NC_TRACE_SILK
C5: 0.1uF; 0603
D1, D2, D3, D4: BLUE; LED-0603
D11: RED; LED-0603
FD1, FD2, FD3, FD4: FIDUCIAL1X2; FIDUCIAL-1X2
FRAME1: FRAME-LETTER; CREATIVE_COMMONS
I2C0: JUMPER-SMT_3_2-NC_TRACE_SILK; SMT-JUMPER_3_2-NC_TRACE_SILK
J1: 1X04_NO_SILK
J2, J3: Qwiic Right Angle; JST04_1MM_RA
J4: 1X01_NO_SILK
J9: AVR_SPI_PROG_3X2TESTPOINTS; 2X3_TEST_POINTS
JP1, JP2, JP3, JP4, JP5, JP6, JP7, JP8: STAND-OFF
K1, K2, K3, K4: Solid State Relay - 40A; SSR-40DA-H
LOGO1: SFE_LOGO_NAME1_INCH; SFE_LOGO_NAME_1
LOGO2: OSHW-LOGOS; OSHW-LOGO-S
PWR0: JUMPER-SMT_2_NC_TRACE_SILK; SMT-JUMPER_2_NC_TRACE_SILK
Q1, Q2, Q3, Q4: 600mA/40V; SOT23-3
R1, R3, R4, R6, R7, R9, R10, R11, R13: 1k; 0603
R2, R5, R8, R12: 47; 0603
R14, R15, R17: 4.7k; 0603
U4: ATTINY84-ARDUINO; SO14
U$1: SFE_LOGO_NAME_FLAME_.4
U$2, U$3, U$4: QUAD_SOLID_STATE_RELAY0
U$5, U$9: 11
U$6, U$10: 22
U$7, U$11: 33
U$8, U$12: 44
U$13, U$14: GND_P
U$15: I2C
U$16, U$17: 3V3_P
U$18, U$19: SCL_IO
U$20, U$21: SDA_IO
U$22: PWR_TO
U$23: ADR3
U$24, U$25: !RST_I

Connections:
3.3V: C5.1, D11.A, I2C0.2, J1.3, J2.2, J3.2, J9.2, K1.3, K2.3, K3.3, K4.3, R1.2, R4.2, R7.2, R10.2, R17.1, U4.1
ADDR_JUMP: ADR0.1, U4.6
GND: ADR0.2, C5.2, J1.4, J2.1, J3.1, J9.6, PWR0.1, Q1.2, Q2.2, Q3.2, Q4.2, U4.14
MISO: J9.1, U4.8
unnamed: D2.C, Q2.3, R5.1
unnamed: D1.C, Q1.3, R2.1
unnamed: K1.4, R5.2
unnamed: D2.A, R4.1
unnamed: D3.C, Q3.3, R8.1
unnamed: K3.4, R8.2
unnamed: D1.A, R1.1
unnamed: D3.A, R7.1
unnamed: D4.C, Q4.3, R12.1
unnamed: K2.4, R2.2
unnamed: K4.4, R12.2
unnamed: D4.A, R10.1
unnamed: D11.C, R11.1
unnamed: PWR0.2, R11.2
unnamed: I2C0.3, R15.1
unnamed: I2C0.1, R14.1
OPTO_1: Q1.1, R3.1
OPTO_2: Q2.1, R6.1
OPTO_3: Q3.1, R9.1
OPTO_4: Q4.1, R13.1
RELAY_CTRL1: R3.2, U4.10
RELAY_CTRL2: R6.2, U4.11
RELAY_CTRL3: R9.2, U4.12
RELAY_CTRL4: R13.2, U4.13
SCL/SCK: J1.1, J2.4, J3.4, J9.3, R15.2, U4.9
SDA/MOSI: J1.2, J2.3, J3.3, J9.4, R14.2, U4.7
~RESET: J4.1, J9.5, R17.2, U4.4
